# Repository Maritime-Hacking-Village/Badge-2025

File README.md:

# Differential Destroyer
This document attempts to provide an overview of the MHV badge this year. We're going to go over the features of the board, walk through the board layout, and dive into the firmware interfaces and scriping engine. Please note that this documentation, along with the firmware itself, is very much a work-in-progress. As we continue to develop the board's firmware, we will be updating these docs and the scripting interface. *All voltage glitching functions are experimental and may cause damage if used improperly. We assume no liability for damages caused by performing voltage glitching.*

## *Important Notice!*
If there is a missing feature that you desperately want implemented during DEF CON, or if you run into bugs, please approach @nick-halt and I'd be happy to help get your board working as desired, time permitting.

## *SAFETY WARNING*
The diferential injector circuit is *not* electrially isolated from the connected device or bus. You should not connect this device directly to a boat without additional safety precautions.

The injector circuit can drive 400mA maximum output current. This is enough to be dangerous in certain circumstances. Please do not use the injector mode without a robust understanding of what you're doing and assurance that you're operating the device safely. Please refer to the provided schematics.

Absolutely do not attempt fault injection using the injector circuit on the CTF equipment at the village, or without explicit and informed permission from the device's handler.

## Features
### Hardware
The hardware contains the following:

- Pico 2 compatible headers.
  - All boards sold through the village will come bundled with a Pico 2 flashed with the current version of firmware. If you want to BYOD here, please approach village staff and we'll gladly flash your board.
- 1.9" 320x170 TFT LCD display
- 5-bit joystick input
- 2 buttons
- 9 WS2812B NeoPixels
- Accelerometer
- SAO connector bridged to the Pico 2 and I2C bus
- SD card slot
- Battery charging capability with a 2-pin JST-PH connector
- Two 3-pin (H, L, GND) screw terminal ports for differentially modulated protocols
  - One Trx, one Rx connector
    - Digitally controlled Trx-Rx tie switch to switch between full-duplex and half-duplex mode
  - EMI protection circuit
  - Digitally controlled termination resistors (120R, 220R, 13R, or open)
  - MCP2518FD CAN-FD transceiver
  - Differential receiver circuit to decode arbitrary differential signals
  - Differential injector circuit to encode arbitrary differential signals
    - Operates up to 5 MHz
    - Digitally switched voltage references (0V, 1V, 1V5, 2V, 2V5, 3V, 3V5, 4V)
    - Digitally switched high impedance mode
- Licensed under the CERN-OHL-W

#### LED Behavior
Along with the 9 NeoPixels, we have 6 additional single-color LEDs.

- Battery: to the left of the Pico 2, there is a battery charge status indicator LED. This will be solid amber when charging, off when discharging, and oscillating when the battery is unplugged (we are aware this blinks like crazy)
- Differential Injector: on the Pico 2, by the USB connector, there is a green LED that will blink when the differential injector circuit is actively transmitting
- CAN Tx/Rx: by the right lanyard strap, there are two LEDs indicating whether the CAN SPI transceiver is transmitting or receiving frames. Note that this will *not* blink when using the differential injector/receiver circuit directly, but rather the CAN SPI transceiver.
- Differential Receiver: to the right of the CAN Tx/Rx LEDs, there is an LED indicating the presence of data on the differential receiver circuit.

### Firmware
The firmware contains the following:

- Available Rust source code under the Apache 2.0 & MIT licenses
- Cooperative scheduler using the embassy-rs runtime
- Scrolling console display drivers for log output
- USB serial device pass-through for log output
- Embedded scripting engine using Rhai (rhai.rs)
  - USB serial device pass-through for embedded scripting engine
  - Script bindings to inputs, peripherals, and the Trx/Rx circuit
- Some secrets :^)

#### TODOs
The firmware is not complete yet. We'll be updating this repository as we have time to expand firmware capability. We are currently absent an implementation for the following:

- SD card FAT32 file system for packet captures and replay files
- Button-controlled GUI
- More/better protocol state machines
  - Missing Modbus Rx
- MCP2518FD drivers
- Better I2C/SPI pass-through
- Better docs (like this one)

## Scripting Engine
We chose Rhai for our scripting language for its seamless integration into our Rust firmware. Some functions require switching from the firmware's default application context to user control.

Let's enumerate the full set:

| Function | Args | Returns | Description | Requires Control? |
|--|--|--|--|--|
| `sys::assume_control` | `()` | `()` | Takes control of app context | false |
| `sys::release_control` | `()` | `()` | Releases control of app context | true |
| `sys::random` | `(bytes: INT)` | `Blob` | Samples the TRNG | false |
| `sys::time` | `()` | `FLOAT` | Samples RTC | false |
| `sys::ticks` | `()` | `INT` | Samples clock counter | false |
| `sys::sleep` | `(secs: FLOAT)` | `()` | Suspends script execution | false |
| `sys::heap` | `()` | `Array` | Probes the heap [used, free] | false |
| `input::read` | `()` | `Dynamic` | Polls user input (joystick, buttons) | false |
| `sao::get_direction` | `()` | `Array` | Returns SAO GPIO pin direction [pin 1, pin 2] | false |
| `sao::set_direction` | `(dir_1: bool, dir_2: bool)` | `()` | Sets SAO GPIO pin direction | false |
| `sao::read` | `()` | `Array` | Reads SAO GPIO | false |
| `sao::write` | `(out_1: bool, out_2: bool)` | `()` | Writes to SAO GPIO | false |
| `display::set_backlight` | `(percent: INT \| float)` | `()` | Sets display backlight percentage | false |
| `display::set_pixel` | `(x: INT, y: INT, r: INT, g: INT, b: INT)` | `()` | Sets a pixel | true |
| `display::fill_region` | `(sx: INT, ex: INT, sy: INT, ey: INT, r: INT, g: INT, b: INT)` | `()` | Fills in a rectangle | true |
| `display::clear` | `()` | `()` | Clears the display | true |
| `display::flush` | `()` | `()` | Flushes the display | true |
| `display::reset` | `()` | `()` | Resets the display | false |
| `console::write` | `(text: &str \| Array)` | `()` | Writes to display as a console; supports ANSI escape codes | true |
| `led::set` | `(i: INT, r: INT, g: INT, b: INT)` | `()` | Sets the given LED | true |
| `accel::read` | `()` | `Dynamic` | Polls the accelerometer | false |
| `accel::set_reg8` | `(reg: INT, value: INT)` | `()` | Sets an 8-bit register | true |
| `accel::set_reg16` | `(reg: INT, value: INT)` | `()` | Sets a 16-bit register | true |
| `accel::set_int_enable` | `(tilt: bool, flip: bool, anym: bool, shake: bool, tilt35: bool, auto_clr: bool, acq: bool)` | `()` | Enables desired accelerometer interrupts | true |
| `accel::set_mode` | `(mode: INT, i2c_wdt_neg: bool, i2c_wdt_pos)` | `()` | Sets mode (sleep, standby, wake) | true |
| `accel::set_sample_rate` | `(rate: INT)` | `()` | Sets sample rate | true |
| `accel::set_motion_control` | `(reset: bool, raw_proc_stat: bool, z_axis_ort: bool, tilt35_en: bool, shake_en: bool, anym: bool, motion_latch: bool, tiltflip: bool)` | `()` | Enables motion capture | true |
| `accel::set_anym_threshold` | `(threshold: INT)` | `()` | Any motion threshold | true |
| `accel::set_anym_debounce` | `(debounce: INT)` | `()` | Any motion debounce | true | true |
| `accel::set_shake_threshold` | `(threshold: INT)` | `()` | Shake threshold | true |
| `accel::set_shake_duration` | `(cnt: INT, p2p: INT)` | `()` | Shake duration | true |
| `batt::status` | `()` | `Dynamic` | Reads the battery status registers | false |
| `trx::get_term` | `()` | `Array` | Get the termination switch values | true |
| `trx::set_term` | `(sel_0: bool, sel_1: bool)` | `()` | Set termintation resistor value | true |
| `trx::get_tie` | `()` | `bool` | Is the tie enabled? | true |
| `trx::set_tie` | `(tied: bool)` | `()` | Set the Trx-Rx tie | true |
| `tx::is_enabled` | `()` | `bool` | Is Tx enabled? | true |
| `tx::enable` | `()` | `()` | Enable Tx | true |
| `tx::disable` | `()` | `()` | Disable Tx | true |
| `tx::get_baud` | `()` | `INT` | Get Tx baud | true |
| `tx::set_baud` | `(baud: INT)` | `()` | Set Tx baud | true |
| `tx::set_baud` | `(baud: INT)` | `()` | Set the operating frequency of the Tx module | true |
| `tx::get_mode` | `()` | `ImmutableString` | Gets the current mode | false |
| `tx::set_mode` | `(mode: &str)` | `()` | Sets the operating mode ("can" or "inject") | true |
| `tx::send` | `(data: Blob)` | `()` | Sends the bytestream; behavior dependent on mode | true |
| `rx::is_enabled` | `()` | `bool` | Is Rx enabled? | true |
| `rx::get_baud` | `()` | `INT` | Get Rx baud | true |
| `rx::set_baud` | `(baud: INT)` | `()` | Set Rx baud | true |
| `rx::enable` | `()` | `()` | Enable Rx | true |
| `rx::disable` | `()` | `()` | Disable Rx | true |
| `rx::set_mode` | `(mode: &str)` | `()` | Sets the operating mode ("can" or "nmea0183") | true |
| `rx::get_mode` | `()` | `ImmutableString` | Gets the current mode | false |
| `rx::recv` | `(timeout_secs: FLOAT)` | `Blob` | Waits for a message to be received and returns the bytestream | true |
| `can::encode` | `(arb_id: INT, rtr: bool, payload: Blob)` | `Blob` | Encodes a CAN 2.0B message for use by the "can" Tx operating mode | false |

### Constants
We also expose some constants for ease-of-use:

| Const | Value | Description |
|--|--|--|
| `trx::TERM_OPEN_0` | `false` | H/L open |
| `trx::TERM_OPEN_1` | `false` | H/L open |
| `trx::TERM_120R_0` | `true` | 120R termination (CAN/NMEA-2000) |
| `trx::TERM_120R_1` | `false` | 120R termination (CAN/NMEA-2000) |
| `trx::TERM_220R_0` | `false` | 220R termination (Modbus) |
| `trx::TERM_220R_1` | `true` | 220R termination (Modbus) |
| `trx::TERM_13R_0` | `true` | 13R termination *(close to shorted)* |
| `trx::TERM_13R_1` | `true` | 13R termination *(close to shorted)* |
| `tx::L_Z0` | `0b000_0_000_1` | Set high-impedance mode on L |
| `tx::L_0V` | `0b000_0_000_0` | Set L to 0V |
| `tx::L_1V` | `0b000_0_100_0` | Set L to 1V |
| `tx::L_1V5` | `0b000_0_010_0` | Set L to 1.5V |
| `tx::L_2V` | `0b000_0_110_0` | Set L to 2V |
| `tx::L_2V5` | `0b000_0_001_0` | Set L to 2.5V |
| `tx::L_3V` | `0b000_0_101_0` | Set L to 3V |
| `tx::L_3V5` | `0b000_0_011_0` | Set L to 3.5V |
| `tx::L_4V` | `0b000_0_111_0` | Set L to 4V |
| `tx::H_Z0` | `0b000_1_000_0` | Set high-impedance mode on H |
| `tx::H_0V` | `0b000_0_000_0` | Set H to 0V |
| `tx::H_1V` | `0b100_0_000_0` | Set H to 1V |
| `tx::H_1V5` | `0b010_0_000_0` | Set H to 1.5V |
| `tx::H_2V` | `0b110_0_000_0` | Set H to 2V |
| `tx::H_2V5` | `0b001_0_000_0` | Set H to 2.5V |
| `tx::H_3V` | `0b101_0_000_0` | Set H to 3V |
| `tx::H_3V5` | `0b011_0_000_0` | Set H to 3.5V |
| `tx::H_4V` | `0b111_0_000_0` | Set H to 4V |
| `tx::LOW_Z` | `0b111_0_111_0` | Bitmask to turn off high-impedance mode |

### Caveats
The heap is pretty small on the stock Pico 2, and we still need to make a few optimization passes to reduce the firmware's memory footprint, so you'll likely run into memory problems with sufficienty complex Rhai scripts. Please approach village staff with any debugging -- we appreciate the feedback.

### Guided Tour
So to get access to the scripting engine, first plug your Pico 2 into your machine over USB and connect to one of the serial ports that comes up (the other is the log output):

```
picocom --imap lfcrlf --echo /dev/ttyACM2
```

You should be greeted by a splash screen welcoming you to the REPL.

Now, let's take control of the application context:

```
sys::assume_control()
```

You can release control back to the firmware with (or Ctrl-D):

```
sys::release_control()
```

Great. Let's see what we can do.

#### LEDs
Let's write a simple loop to blink our LEDs:
```
for i in 0..10 { for j in 0..9 { led::set(j, i * 25, 127, j * 25) }; sys::sleep(0.5); }
```

#### CAN
```
let data = sys::random(8);
let frame = can::encode(0x8AA, false, data);
tx::set_mode("can")
tx::set_baud(250_000)
tx::enable()
tx::send(frame)
```

```
// Half-duplex mode
trx::set_tie(true)
// 120R termination resistor for CAN
trx::set_term(trx::TERM_120R_0, trx::TERM_120R_1)
rx::set_mode("can")
rx::set_baud(250_000)
rx::enable()
let frame = rx::recv(5.0)
print(frame)
```

Note that you can separate multi-line strings in the REPL with `\`.

#### Differential Injector
```
let data = blob();
data.push(tx::H_4V | rx::L_1V);
data.push(tx::H_3V5 | rx::L_1V5);
data.push(tx::H_3V | rx::L_2V);
data.push(tx::H_2V5 | rx::L_2V5);
data.push(tx::H_2V | rx::L_3V);
data.push(tx::H_1V5 | rx::L_3V5);
data.push(tx::H_1V | rx::L_4V);
data.push(tx::H_1V5 | rx::L_3V5);
data.push(tx::H_2V | rx::L_3V);
data.push(tx::H_2V5 | rx::L_2V5);
data.push(tx::H_3V | rx::L_2V);
data.push(tx::H_3V5 | rx::L_1V5);
data.push(tx::H_4V | rx::L_1V);
tx::set_mode("inject");
tx::set_baud(1_000_000);
tx::enable();
tx::send(data);
```

```
let flag = blob()
// SOF
flag.push(tx::H_1V | tx::L_1V); flag.push(tx::H_1V | tx::L_1V); flag.push(tx::H_1V | tx::L_1V);
// M
flag.push(tx::H_4V | tx::L_1V); flag.push(tx::H_3V5 | tx::L_2V5); flag.push(tx::H_3V | tx::L_2V); flag.push(tx::H_3V5 | tx::L_2V5); flag.push(tx::H_4V | tx::L_1V);
// IFS
flag.push(tx::H_1V | tx::L_1V); flag.push(tx::H_1V | tx::L_1V);
// H
flag.push(tx::H_4V | tx::L_1V); flag.push(tx::H_2V5 | tx::L_2V); flag.push(tx::H_2V5 | tx::L_2V); flag.push(tx::H_4V | tx::L_1V);
// IFS
flag.push(tx::H_1V | tx::L_1V); flag.push(tx::H_1V | tx::L_1V);
// V
flag.push(tx::H_4V | tx::L_1V); flag.push(tx::H_2V | tx::L_1V); flag.push(tx::H_1V | tx::L_1V); flag.push(tx::H_2V | tx::L_1V); flag.push(tx::H_4V | tx::L_1V);
// IFS
flag.push(tx::H_1V | tx::L_1V); flag.push(tx::H_1V | tx::L_1V); flag.push(tx::H_1V | tx::L_1V);
tx::set_mode("inject");
tx::set_baud(1_000_000);
tx::enable();
tx::send(flag);
```

#### Accelerometer
```
// Shake up the board to see measurements.
for i in 0..50 { print(accel::read()); sys::sleep(0.1); }
```

#### Input
```
for i in 0..50 { print(input::read()); sys::sleep(0.1); }
```

### Display/Console
```
display::clear();
display::flush();
console::write("\x1B[32Hack the planet!");
display::fill_region(50, 100, 50, 100, 127, 0, 127);
display::flush();
for i in 0..20 { for j in 0..20 { display::set_pixel(100 + i, 100 + j, i*10, j*10, 64); }}
display::flush();
```

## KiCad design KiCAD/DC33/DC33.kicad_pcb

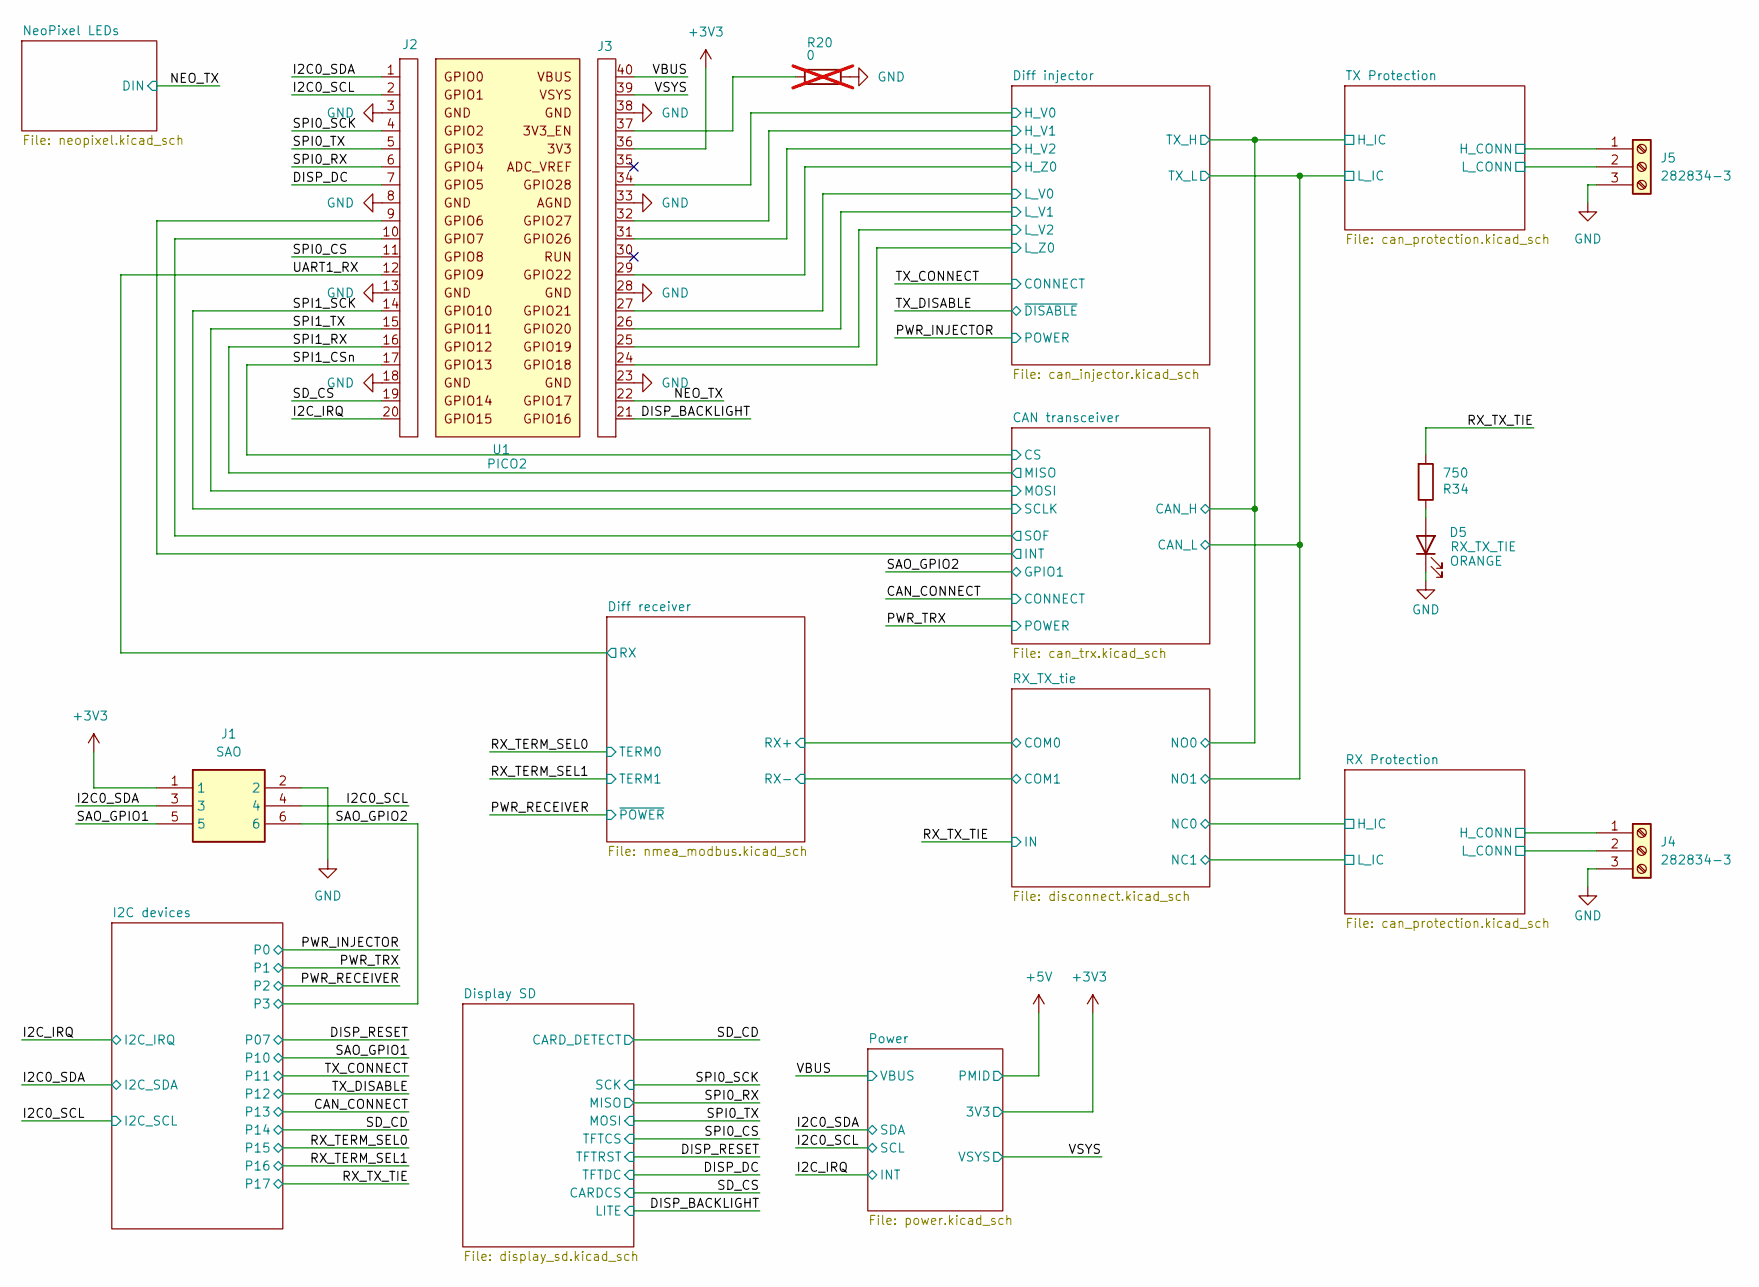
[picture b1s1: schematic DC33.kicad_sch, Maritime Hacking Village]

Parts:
D5: 1.8V/2MA ORANGE; LED_0603_1608Metric; Manufacturer Part Number APT1608LSECK/J4-PRV
J1: SAO; SFH11-NBPC-D03-ST-BK; Manufacturer Part Number SFH11-NBPC-D03-ST-BK
J2: PPTC201LFBN-RC; RPi_Pico_SMD_TH_L; Manufacturer Part Number PPTC201LFBN-RC
J3: PPTC201LFBN-RC; RPi_Pico_SMD_TH_R; Manufacturer Part Number PPTC201LFBN-RC
J4, J5: 282834-3; 2828343; Manufacturer Part Number 282834-3
R20: 0; R_0603_1608Metric; Tolerance 1%; Manufacturer Part Number ERJ-3GEY0R00V; not fitted
R34: 750; R_0603_1608Metric; Tolerance 1%; Manufacturer Part Number ERJ-3EKF7500V
U1: PICO2; Manufacturer Part Number PICO2

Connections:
+3V3: J1.1, J3.36; also elsewhere on the board
/CAN transceiver/INT: J2.9; also elsewhere on the board
/CAN transceiver/SOF: J2.10; also elsewhere on the board
/DISP_BACKLIGHT: J3.21; also elsewhere on the board
/DISP_DC: J2.7; also elsewhere on the board
/Diff injector/H_V0: J3.34; also elsewhere on the board
/Diff injector/H_V1: J3.32; also elsewhere on the board
/Diff injector/H_V2: J3.31; also elsewhere on the board
/Diff injector/H_Z0: J3.29; also elsewhere on the board
/Diff injector/L_V0: J3.27; also elsewhere on the board
/Diff injector/L_V1: J3.26; also elsewhere on the board
/Diff injector/L_V2: J3.25; also elsewhere on the board
/Diff injector/L_Z0: J3.24; also elsewhere on the board
/I2C0_SCL: J1.4, J2.2; also elsewhere on the board
/I2C0_SDA: J1.3, J2.1; also elsewhere on the board
/I2C_IRQ: J2.20; also elsewhere on the board
/NEO_TX: J3.22; also elsewhere on the board
/RX Protection/H_CONN: J4.1; also elsewhere on the board
/RX Protection/L_CONN: J4.2; also elsewhere on the board
/RX_TX_TIE: R34.2; also elsewhere on the board
/SAO_GPIO1: J1.5; also elsewhere on the board
/SAO_GPIO2: J1.6; also elsewhere on the board
/SD_CS: J2.19; also elsewhere on the board
/SPI0_CS: J2.11; also elsewhere on the board
/SPI0_RX: J2.6; also elsewhere on the board
/SPI0_SCK: J2.4; also elsewhere on the board
/SPI0_TX: J2.5; also elsewhere on the board
/SPI1_CSn: J2.17; also elsewhere on the board
/SPI1_RX: J2.16; also elsewhere on the board
/SPI1_SCK: J2.14; also elsewhere on the board
/SPI1_TX: J2.15; also elsewhere on the board
/TX Protection/H_CONN: J5.1; also elsewhere on the board
/TX Protection/L_CONN: J5.2; also elsewhere on the board
/UART1_RX: J2.12; also elsewhere on the board
/VBUS: J3.40; also elsewhere on the board
GND: D5.1 (K), J1.2, J2.3, J2.8, J2.13, J2.18, J3.23, J3.28, J3.33, J3.38, J4.3, J5.3, R20.2; also elsewhere on the board
unnamed: D5.2 (A), R34.1
unnamed: J3.37, R20.1
VSYS: J3.39; also elsewhere on the board

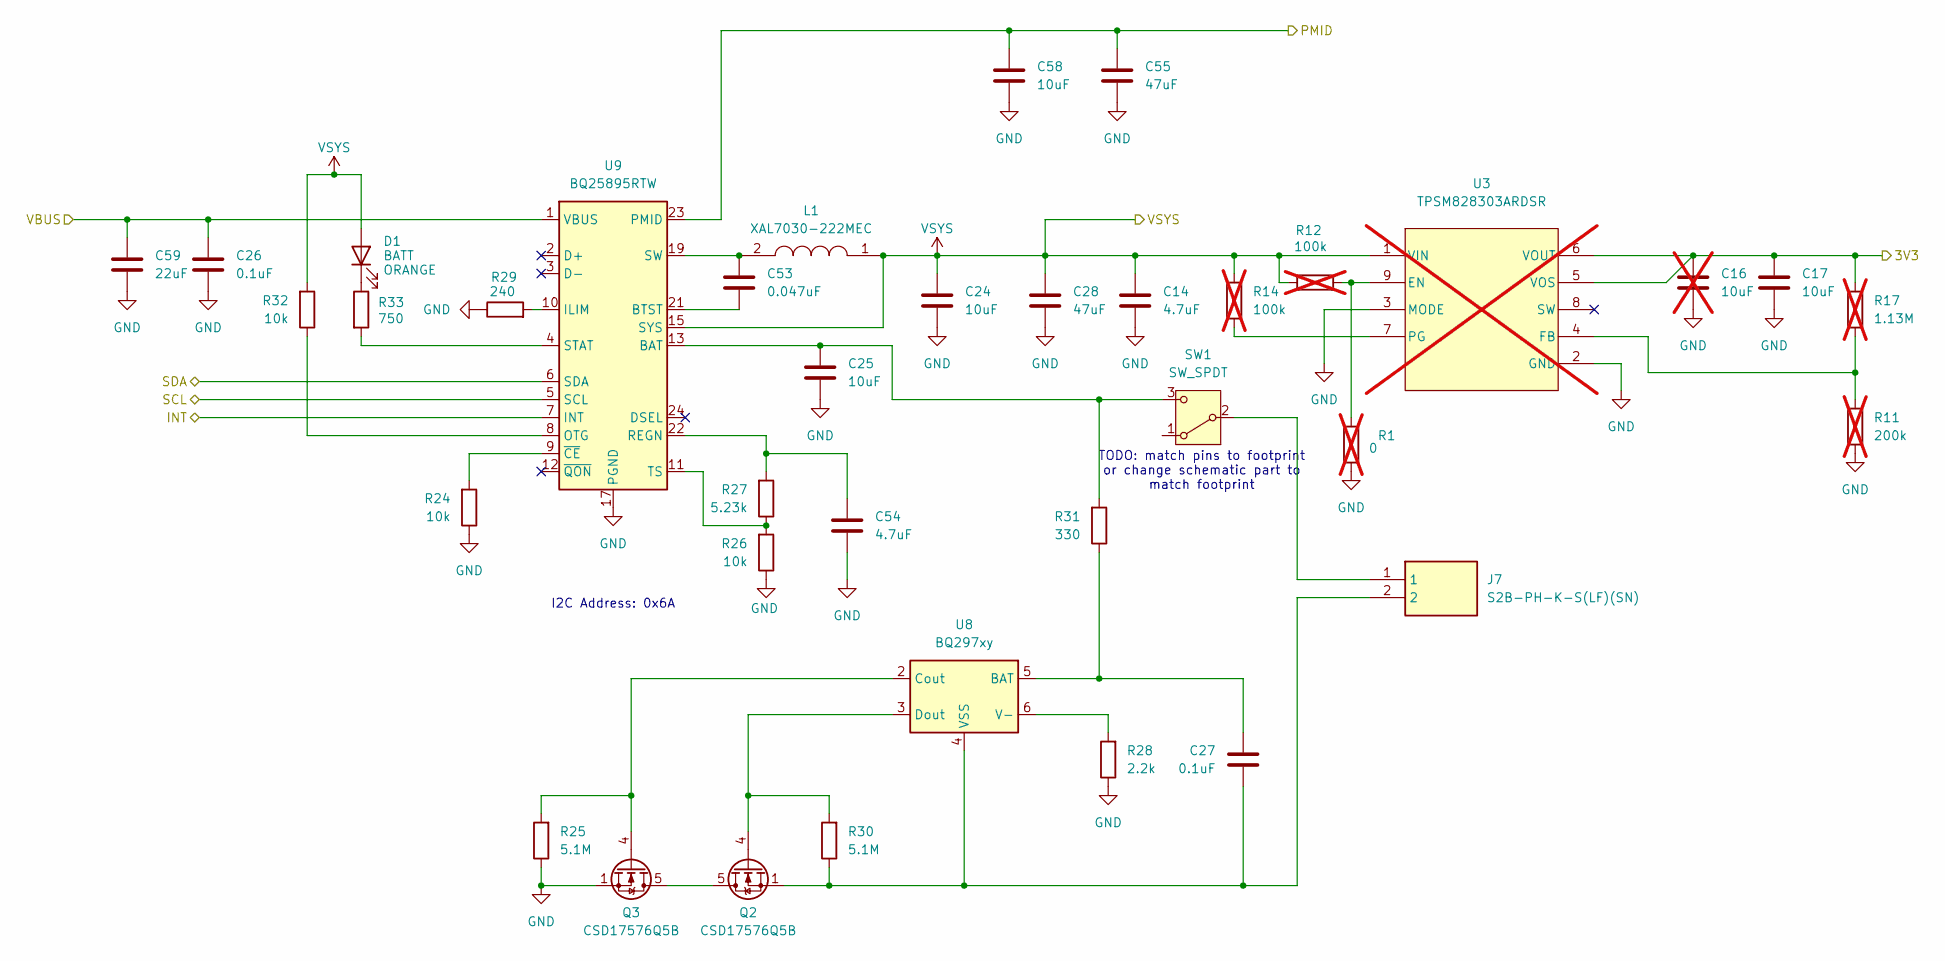
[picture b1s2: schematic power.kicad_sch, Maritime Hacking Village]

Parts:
C14, C54: 4.7uF; C_0603_1608Metric; Manufacturer Part Number CGA3E1X5R0J475K080AC
C16: 10uF; C_0603_1608Metric; Manufacturer Part Number GRM188R61E106MA73J; not fitted
C17, C24, C25, C58: 10uF; C_0603_1608Metric; Manufacturer Part Number GRM188R61E106MA73J
C26, C27: 0.1uF; C_0603_1608Metric; Manufacturer Part Number KGM15BR71E104KT
C28, C55: 47uF; C_0603_1608Metric; Manufacturer Part Number 06036D476MAT2A
C53: 0.047uF; C_0603_1608Metric; Manufacturer Part Number CC0603KRX7R9BB473
C59: 22uF; C_0603_1608Metric; Manufacturer Part Number C1608X5R1A226M080AC
D1: 1.8V/2MA ORANGE; LED_0603_1608Metric; Manufacturer Part Number APT1608LSECK/J4-PRV
J7: S2B-PH-K-S(LF)(SN); SHDRRA2W50P0X200_1X2_590X760X480P; Manufacturer Part Number S2B-PH-K-S(LF)(SN)
L1: XAL7030-222MEC; XAL7030272MEB; Manufacturer Part Number XAL7030-222MEC
Q2, Q3: CSD17576Q5B; TDSON-8-1; Manufacturer Part Number CSD17576Q5B
R1: 0; R_0603_1608Metric; Tolerance 1%; Manufacturer Part Number ERJ-3GEY0R00V; not fitted
R11: 200k; R_0603_1608Metric; Tolerance 1%; Manufacturer Part Number ERJ-3EKF2003V; not fitted
R12, R14: 100k; R_0603_1608Metric; Tolerance 1%; Manufacturer Part Number ERJ-3EKF1003V; not fitted
R17: 1.13M; R_0603_1608Metric; Tolerance 1%; Manufacturer Part Number CRCW06031M13FKEA; not fitted
R24, R26, R32: 10k; R_0603_1608Metric; Tolerance 1%; Manufacturer Part Number CRG0603F10K
R25, R30: 5.1M; R_0603_1608Metric; Tolerance 1%; Manufacturer Part Number KTR03EZPF5104
R27: 5.23k; R_0603_1608Metric; Tolerance 1%; Manufacturer Part Number CRCW06035K23FKEA
R28: 2.2k; R_0603_1608Metric; Tolerance 1%; Manufacturer Part Number CRGCQ0603J2K2
R29: 240; R_0603_1608Metric; Tolerance 1%; Manufacturer Part Number RC0603FR-07240RL
R31: 330; R_0603_1608Metric; Tolerance 1%; Manufacturer Part Number RC0603FR-07330RL
R33: 750; R_0603_1608Metric; Tolerance 1%; Manufacturer Part Number ERJ-3EKF7500V
SW1: SW_SPDT; 450404015514
U3: TPSM828303ARDSR; RDS0009A-MFG; Manufacturer Part Number TPSM828303ARDSR; not fitted
U8: BQ297xy; WSON-6_1.5x1.5mm_P0.5mm; Manufacturer Part Number BQ29700DSER
U9: BQ25895RTW; Texas_RTW_WQFN-24-1EP_4x4mm_P0.5mm_EP2.7x2.7mm_ThermalVias; Manufacturer Part Number BQ25895RTWT

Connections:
+3V3: C16.1, C17.1, R17.1, U3.5 (VOS), U3.6 (VOUT); also elsewhere on the board
+5V: C55.1, C58.1, U9.23 (PMID); also elsewhere on the board
/I2C0_SCL: U9.5 (SCL); also elsewhere on the board
/I2C0_SDA: U9.6 (SDA); also elsewhere on the board
/I2C_IRQ: U9.7 (INT); also elsewhere on the board
/VBUS: C26.1, C59.1, U9.1 (VBUS); also elsewhere on the board
GND: C14.2, C16.2, C17.2, C24.2, C25.2, C26.2, C28.2, C54.2, C55.2, C58.2, C59.2, Q3.1 (S), Q3.2 (S), Q3.3 (S), R1.1, R11.2, R24.1, R25.1, R26.1, R28.1, R29.1, U3.2 (GND), U3.3 (MODE), U9.17 (PGND), U9.18 (PGND), U9.25 (PGND); also elsewhere on the board
unnamed: C53.1, L1.2, U9.19 (SW), U9.20 (SW)
unnamed: D1.1 (K), R33.1
unnamed: Q2.5 (D), Q3.5 (D)
unnamed: Q2.4 (G), R30.2, U8.3 (Dout)
unnamed: Q3.4 (G), R25.2, U8.2 (Cout)
unnamed: J7.1, SW1.2 (B)
unnamed: C25.1, R31.2, SW1.3 (C), U9.13 (BAT), U9.14 (BAT)
unnamed: R1.2, R12.2, U3.9 (EN)
unnamed: R11.1, R17.2, U3.4 (FB)
unnamed: R14.2, U3.7 (PG)
unnamed: C27.1, R31.1, U8.5 (BAT)
unnamed: R28.2, U8.6 (V-)
unnamed: C27.2, J7.2, Q2.1 (S), Q2.2 (S), Q2.3 (S), R30.1, U8.4 (VSS)
unnamed: C53.2, U9.21 (BTST)
unnamed: R29.2, U9.10 (ILIM)
unnamed: R32.1, U9.8 (OTG)
unnamed: C54.1, R27.2, U9.22 (REGN)
unnamed: R33.2, U9.4 (STAT)
unnamed: R26.2, R27.1, U9.11 (TS)
unnamed: R24.2, U9.9 (~CE)
VSYS: C14.1, C24.1, C28.1, D1.2 (A), L1.1, R12.1, R14.1, R32.2, U3.1 (VIN), U9.15 (SYS), U9.16 (SYS); also elsewhere on the board

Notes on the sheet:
TODO: match pins to footprint or change schematic part to match footprint
I2C Address: 0x6A

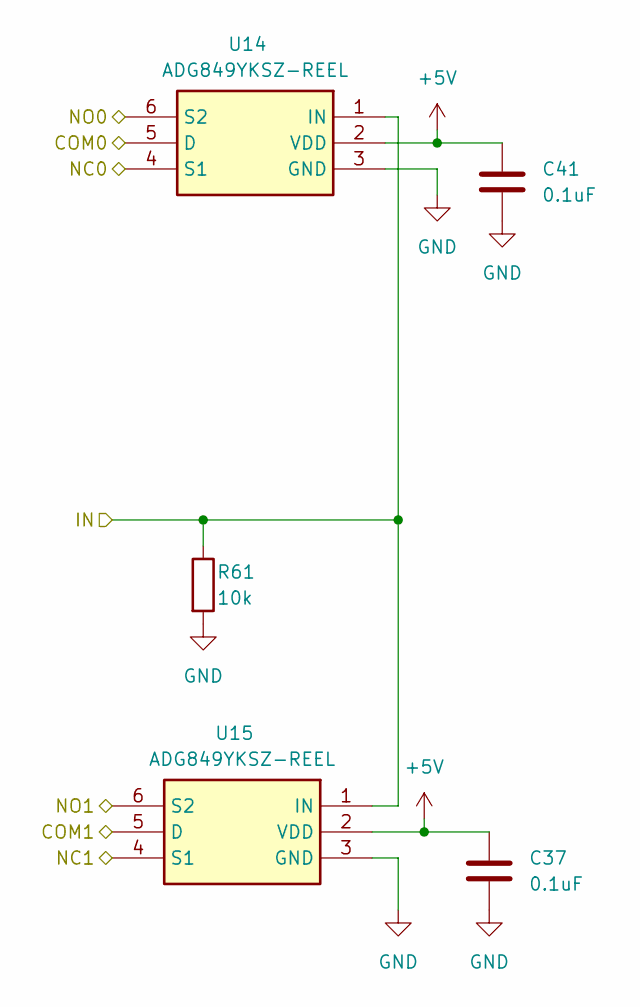
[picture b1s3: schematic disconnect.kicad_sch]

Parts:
C37, C41: 0.1uF; C_0603_1608Metric; Manufacturer Part Number KGM15BR71E104KT
R61: 10k; R_0603_1608Metric; Tolerance 1%; Manufacturer Part Number CRG0603F10K
U14, U15: ADG849YKSZ-REEL; SOT65P210X110-6N; Manufacturer Part Number ADG849YKSZ-REEL

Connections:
+5V: C37.1, C41.1, U14.2 (VDD), U15.2 (VDD); also elsewhere on the board
/CAN transceiver/CAN TRX Disconnect/COM0: U14.5 (D); also elsewhere on the board
/CAN transceiver/CAN TRX Disconnect/COM1: U15.5 (D); also elsewhere on the board
/CAN transceiver/CAN TRX Disconnect/NC0: U14.4 (S1)
/CAN transceiver/CAN TRX Disconnect/NC1: U15.4 (S1)
/CAN transceiver/CAN_H: U15.6 (S2); also elsewhere on the board
/CAN transceiver/CAN_L: U14.6 (S2); also elsewhere on the board
/CAN_CONNECT: R61.1, U14.1 (IN), U15.1 (IN); also elsewhere on the board
GND: C37.2, C41.2, R61.2, U14.3 (GND), U15.3 (GND); also elsewhere on the board

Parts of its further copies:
C13, C32, C38, C42: 0.1uF; C_0603_1608Metric; Manufacturer Part Number KGM15BR71E104KT
R36, R62: 10k; R_0603_1608Metric; Tolerance 1%; Manufacturer Part Number CRG0603F10K
U11, U12, U16, U18: ADG849YKSZ-REEL; SOT65P210X110-6N; Manufacturer Part Number ADG849YKSZ-REEL

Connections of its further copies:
+5V: C13.1, C32.1, C38.1, C42.1, U11.2 (VDD), U12.2 (VDD), U16.2 (VDD), U18.2 (VDD); also elsewhere on the board
/CAN transceiver/CAN_H: U12.6 (S2), U18.6 (S2); also elsewhere on the board
/CAN transceiver/CAN_L: U11.6 (S2), U16.6 (S2); also elsewhere on the board
/Diff injector/Injector Disconnect/COM0: U18.5 (D); also elsewhere on the board
/Diff injector/Injector Disconnect/COM1: U16.5 (D); also elsewhere on the board
/Diff injector/Injector Disconnect/NC0: U18.4 (S1)
/Diff injector/Injector Disconnect/NC1: U16.4 (S1)
/Diff receiver/RX+: U12.5 (D); also elsewhere on the board
/Diff receiver/RX-: U11.5 (D); also elsewhere on the board
/RX Protection/H_IC: U12.4 (S1); also elsewhere on the board
/RX Protection/L_IC: U11.4 (S1); also elsewhere on the board
/RX_TX_TIE: R36.1, U11.1 (IN), U12.1 (IN); also elsewhere on the board
/TX_CONNECT: R62.1, U16.1 (IN), U18.1 (IN); also elsewhere on the board
GND: C13.2, C32.2, C38.2, C42.2, R36.2, R62.2, U11.3 (GND), U12.3 (GND), U16.3 (GND), U18.3 (GND); also elsewhere on the board

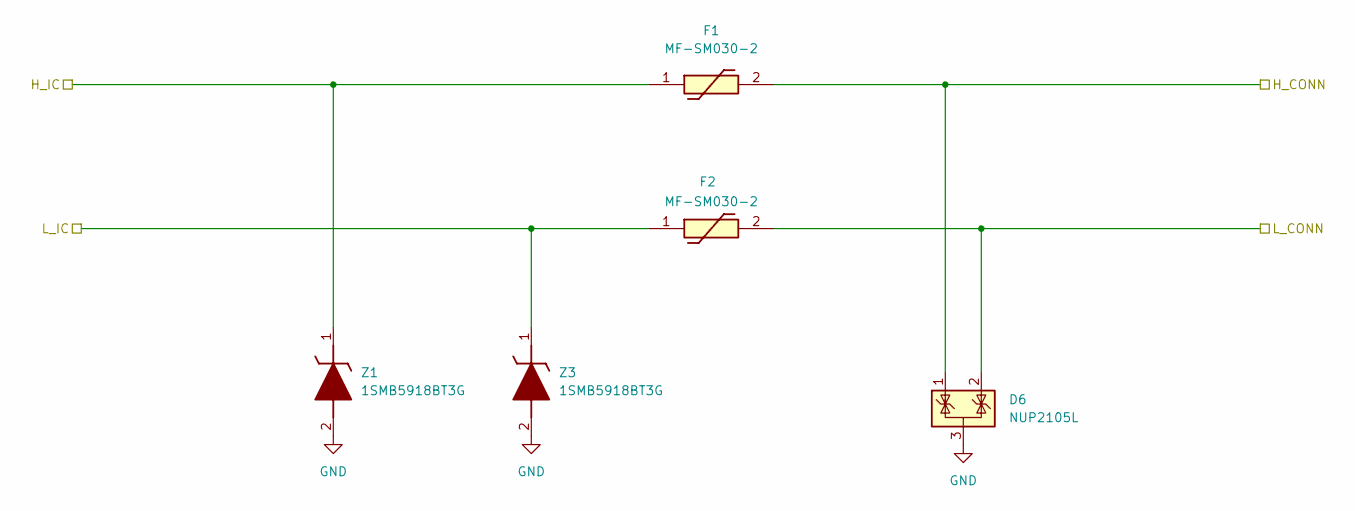
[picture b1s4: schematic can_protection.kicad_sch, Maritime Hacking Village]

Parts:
D6: NUP2105L; SOT-23; Manufacturer Part Number NUP2105LT1G
F1, F2: MF-SM030-2; MFSM0302; Manufacturer Part Number MF-SM030-2
Z1, Z3: 1SMB5918BT3G; DIOM5436X247N; Manufacturer Part Number 1SMB5918BT3G

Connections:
/RX Protection/H_CONN: D6.1 (K), F1.2; also elsewhere on the board
/RX Protection/H_IC: F1.1, Z1.1 (K); also elsewhere on the board
/RX Protection/L_CONN: D6.2 (K), F2.2; also elsewhere on the board
/RX Protection/L_IC: F2.1, Z3.1 (K); also elsewhere on the board
GND: D6.3 (A), Z1.2 (A), Z3.2 (A); also elsewhere on the board

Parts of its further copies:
D7: NUP2105L; SOT-23; Manufacturer Part Number NUP2105LT1G
F3, F4: MF-SM030-2; MFSM0302; Manufacturer Part Number MF-SM030-2
Z2, Z4: 1SMB5918BT3G; DIOM5436X247N; Manufacturer Part Number 1SMB5918BT3G

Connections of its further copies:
/CAN transceiver/CAN_H: F3.1, Z4.1 (K); also elsewhere on the board
/CAN transceiver/CAN_L: F4.1, Z2.1 (K); also elsewhere on the board
/TX Protection/H_CONN: D7.1 (K), F3.2; also elsewhere on the board
/TX Protection/L_CONN: D7.2 (K), F4.2; also elsewhere on the board
GND: D7.3 (A), Z2.2 (A), Z4.2 (A); also elsewhere on the board

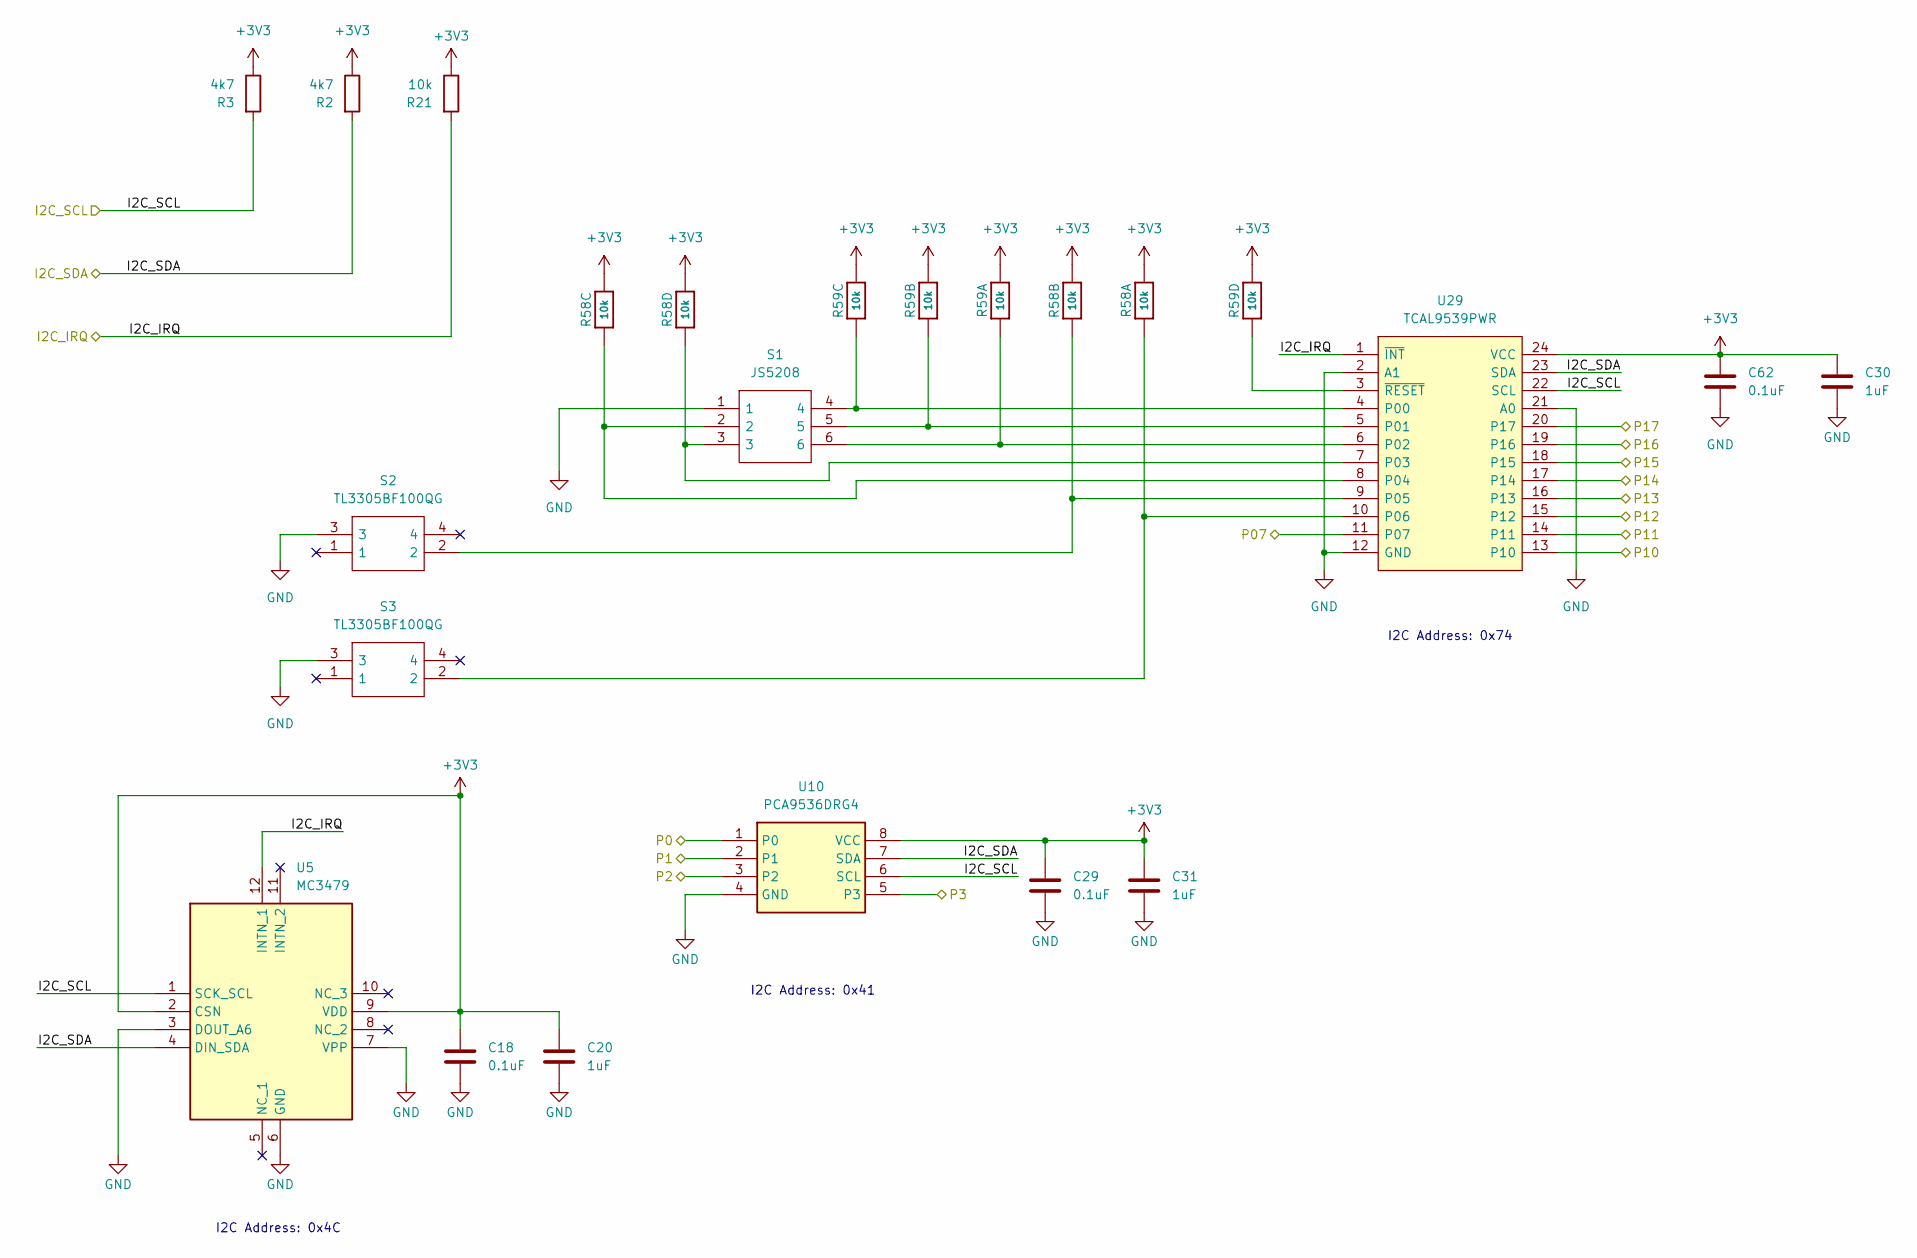
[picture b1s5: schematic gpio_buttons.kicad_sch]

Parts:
C18, C29, C62: 0.1uF; C_0603_1608Metric; Manufacturer Part Number KGM15BR71E104KT
C20, C30, C31: 1uF; C_0603_1608Metric; Manufacturer Part Number CC0603KRX7R9BB105
R2, R3: 4k7; R_0603_1608Metric; Tolerance 1%; Manufacturer Part Number CRG0603F4K7
R21: 10k; R_0603_1608Metric; Tolerance 1%; Manufacturer Part Number CRG0603F10K
R58, R59: 10k; RESPACK_4X0603; Tolerance 1%; Manufacturer Part Number EXB-38V103JV
S1: JS5208; Manufacturer Part Number JS5208
S2, S3: TL3305BF100QG; TL3305BF160QG; Manufacturer Part Number TL3305BF100QG
U5: MC3479; Manufacturer Part Number MC3479
U10: PCA9536DRG4; SOIC127P600X175-8N; Manufacturer Part Number PCA9536DRG4
U29: TCAL9539PWR; SOP65P640X120-24N; Manufacturer Part Number TCAL9539PWR

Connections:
+3V3: C18.1, C20.1, C29.1, C30.1, C31.1, C62.1, R2.1, R3.1, R21.1, R58.5 (2), R58.6 (2), R58.7 (2), R58.8 (2), R59.5 (2), R59.6 (2), R59.7 (2), R59.8 (2), U5.2 (CSN), U5.9 (VDD), U10.8 (VCC), U29.24 (VCC); also elsewhere on the board
/CAN_CONNECT: U29.16 (P13); also elsewhere on the board
/DISP_RESET: U29.11 (P07); also elsewhere on the board
/I2C0_SCL: R3.2, U5.1 (SCK_SCL), U10.6 (SCL), U29.22 (SCL); also elsewhere on the board
/I2C0_SDA: R2.2, U5.4 (DIN_SDA), U10.7 (SDA), U29.23 (SDA); also elsewhere on the board
/I2C_IRQ: R21.2, U5.12 (INTN_1), U29.1 (~INT); also elsewhere on the board
/PWR_INJECTOR: U10.1 (P0); also elsewhere on the board
/PWR_RECEIVER: U10.3 (P2); also elsewhere on the board
/PWR_TRX: U10.2 (P1); also elsewhere on the board
/RX_TERM_SEL0: U29.18 (P15); also elsewhere on the board
/RX_TERM_SEL1: U29.19 (P16); also elsewhere on the board
/RX_TX_TIE: U29.20 (P17); also elsewhere on the board
/SAO_GPIO1: U29.13 (P10); also elsewhere on the board
/SAO_GPIO2: U10.5 (P3); also elsewhere on the board
/SD_CD: U29.17 (P14); also elsewhere on the board
/TX_CONNECT: U29.14 (P11); also elsewhere on the board
/TX_DISABLE: U29.15 (P12); also elsewhere on the board
GND: C18.2, C20.2, C29.2, C30.2, C31.2, C62.2, S1.1, S2.3, S3.3, U5.3 (DOUT_A6), U5.6 (GND), U5.7 (VPP), U10.4 (GND), U29.2 (A1), U29.12 (GND), U29.21 (A0); also elsewhere on the board
unnamed: R58.2 (1), S2.2, U29.9 (P05)
unnamed: R58.3 (1), S1.2, U29.8 (P04)
unnamed: R58.4 (1), S1.3, U29.7 (P03)
unnamed: R59.2 (1), S1.5, U29.5 (P01)
unnamed: R59.3 (1), S1.4, U29.4 (P00)
unnamed: R59.4 (1), U29.3 (~RESET)
unnamed: R59.1, S1.6, U29.6 (P02)
unnamed: R58.1, S3.2, U29.10 (P06)

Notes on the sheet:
I2C Address: 0x4C
I2C Address: 0x74
I2C Address: 0x41

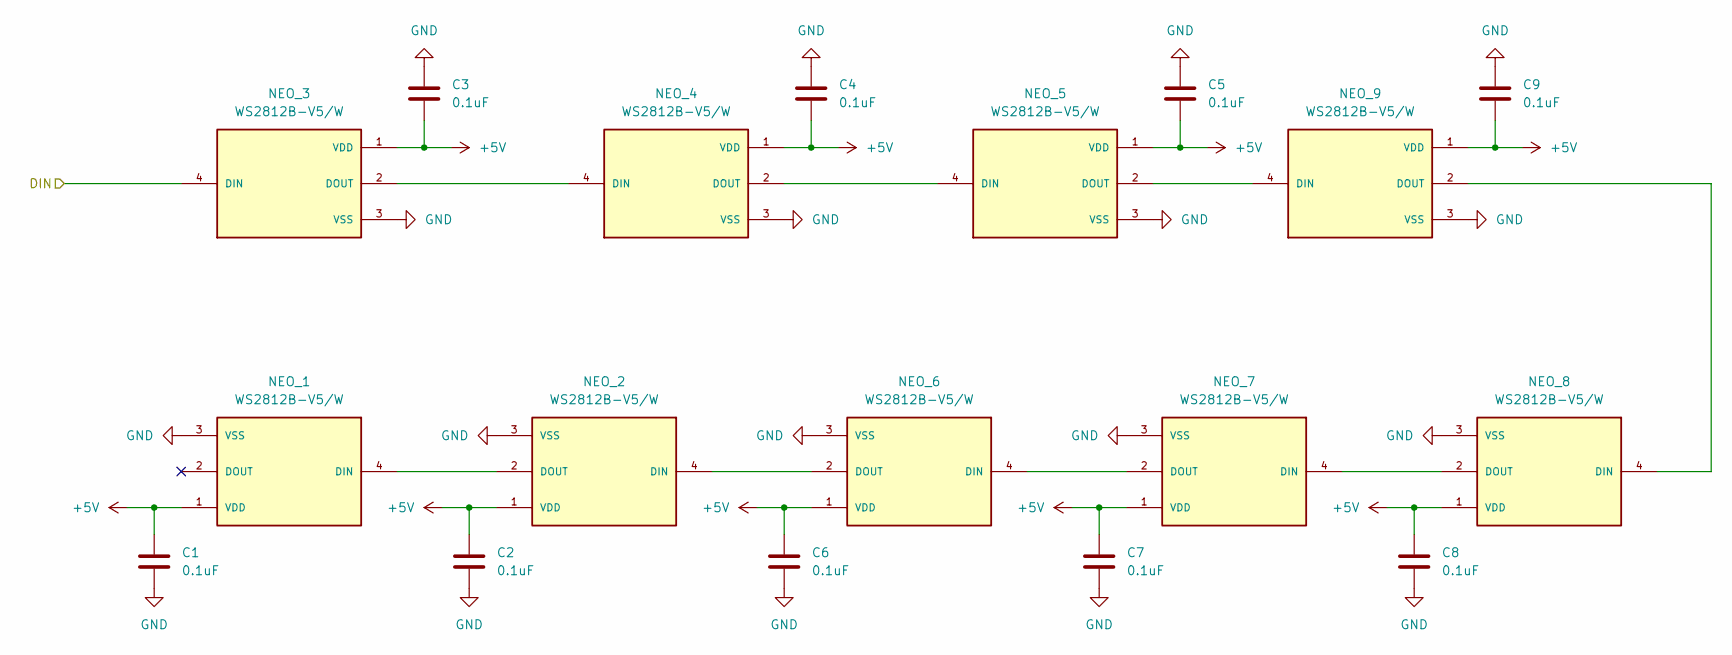
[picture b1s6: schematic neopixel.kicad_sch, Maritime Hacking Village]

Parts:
C1, C2, C3, C4, C5, C6, C7, C8, C9: 0.1uF; C_0603_1608Metric; Manufacturer Part Number KGM15BR71E104KT
NEO_1, NEO_2, NEO_3, NEO_4, NEO_5, NEO_6, NEO_7, NEO_8, NEO_9: WS2812B-V5/W; SOL320P540X170-4N; Manufacturer Part Number WS2812B-V5/W

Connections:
+5V: C1.2, C2.2, C3.2, C4.2, C5.2, C6.2, C7.2, C8.2, C9.2, NEO_1.1 (VDD), NEO_2.1 (VDD), NEO_3.1 (VDD), NEO_4.1 (VDD), NEO_5.1 (VDD), NEO_6.1 (VDD), NEO_7.1 (VDD), NEO_8.1 (VDD), NEO_9.1 (VDD); also elsewhere on the board
/NEO_TX: NEO_3.4 (DIN); also elsewhere on the board
GND: C1.1, C2.1, C3.1, C4.1, C5.1, C6.1, C7.1, C8.1, C9.1, NEO_1.3 (VSS), NEO_2.3 (VSS), NEO_3.3 (VSS), NEO_4.3 (VSS), NEO_5.3 (VSS), NEO_6.3 (VSS), NEO_7.3 (VSS), NEO_8.3 (VSS), NEO_9.3 (VSS); also elsewhere on the board
unnamed: NEO_1.4 (DIN), NEO_2.2 (DOUT)
unnamed: NEO_2.4 (DIN), NEO_6.2 (DOUT)
unnamed: NEO_3.2 (DOUT), NEO_4.4 (DIN)
unnamed: NEO_4.2 (DOUT), NEO_5.4 (DIN)
unnamed: NEO_5.2 (DOUT), NEO_9.4 (DIN)
unnamed: NEO_6.4 (DIN), NEO_7.2 (DOUT)
unnamed: NEO_7.4 (DIN), NEO_8.2 (DOUT)
unnamed: NEO_8.4 (DIN), NEO_9.2 (DOUT)
